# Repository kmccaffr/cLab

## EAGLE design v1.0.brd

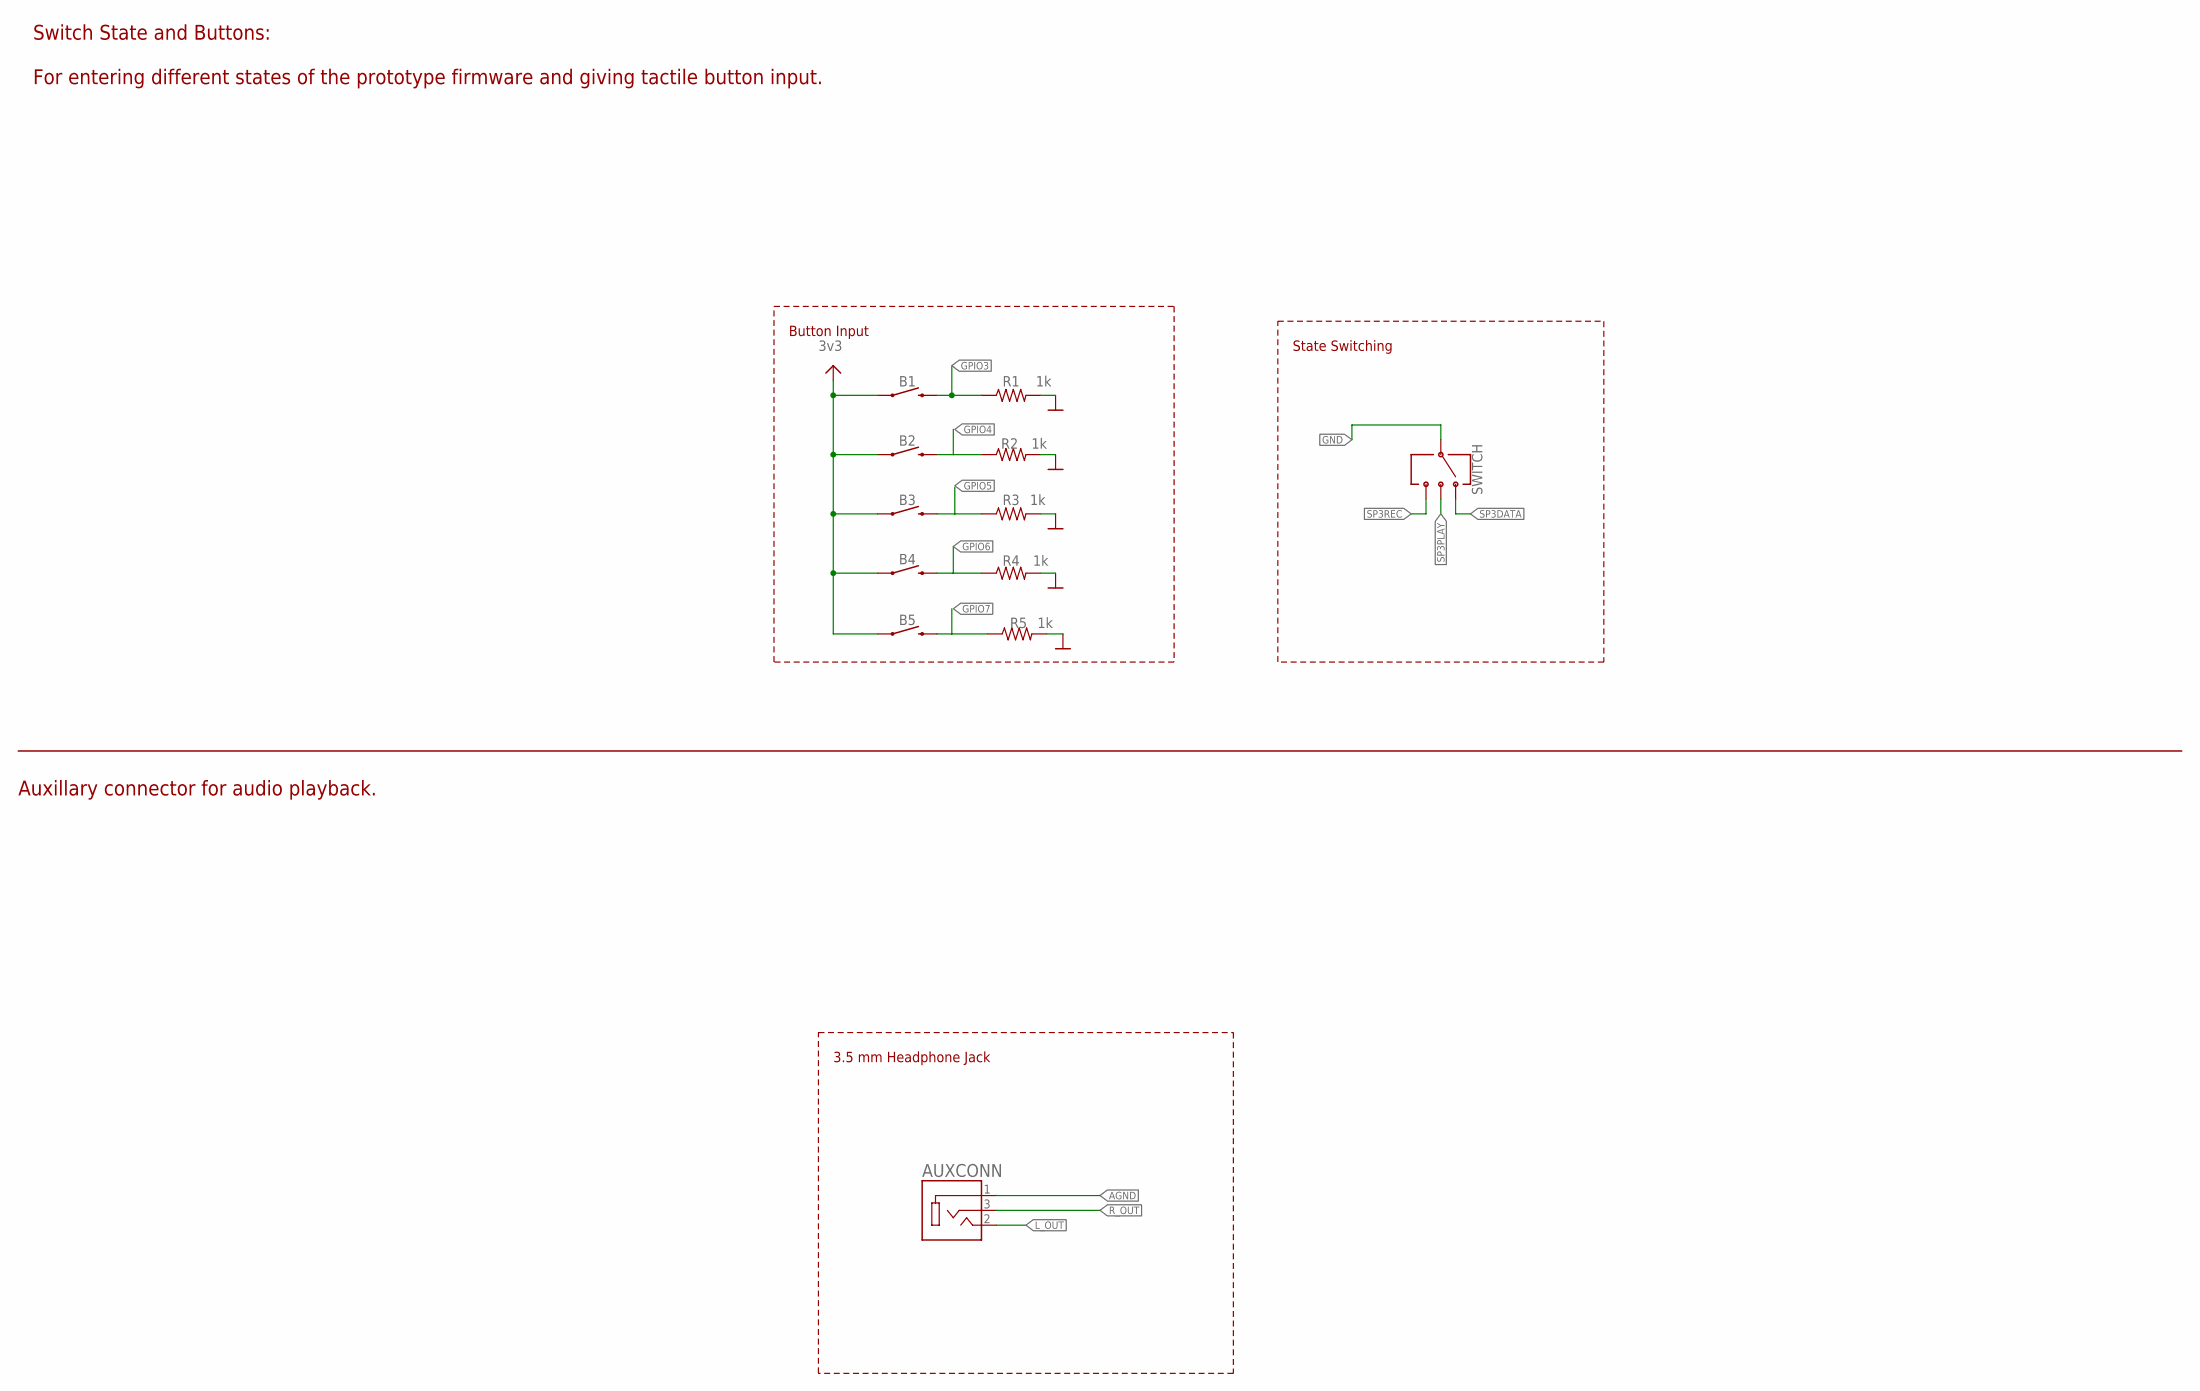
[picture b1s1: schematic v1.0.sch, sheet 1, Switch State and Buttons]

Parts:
AUXCONN: 3.5MM_AUX_JACK; !_SJ-3523-SMT-TR_CUI_SJ-3523-SMT-TR
B1, B2, B3, B4, B5: MOMENTARY-SWITCH-SPST-SMD-6.2MM-TALL; !_TACTILE_SWITCH_SMD_6.2MM_TALL
R1, R2, R3, R4, R5: 1k; !_0603
SWITCH: SWITCH-SP3T-SMD; !SWITCH_SP3T_SMD

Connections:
3.3V: B1.A2 (1), B2.A2 (1), B3.A2 (1), B4.A2 (1), B5.A2 (1); also elsewhere on the board
AGND: AUXCONN.1; also elsewhere on the board
GND: R1.2, R2.2, R3.2, R4.2, R5.2, SWITCH.3; also elsewhere on the board
GPIO3: B1.B2 (2), R1.1; also elsewhere on the board
GPIO4: B2.B2 (2), R2.1; also elsewhere on the board
GPIO5: B3.B2 (2), R3.1; also elsewhere on the board
GPIO6: B4.B2 (2), R4.1; also elsewhere on the board
GPIO7: B5.B2 (2), R5.1; also elsewhere on the board
L_OUT: AUXCONN.2; also elsewhere on the board
R_OUT: AUXCONN.3; also elsewhere on the board
SP3DATA: SWITCH.1; also elsewhere on the board
SP3PLAY: SWITCH.2; also elsewhere on the board
SP3REC: SWITCH.4; also elsewhere on the board

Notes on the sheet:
Button Input
State Switching
3v3
Switch State and Buttons: For entering different states of the prototype firmware and giving tactile button input.
3.5 mm Headphone Jack
Auxillary connector for audio playback.

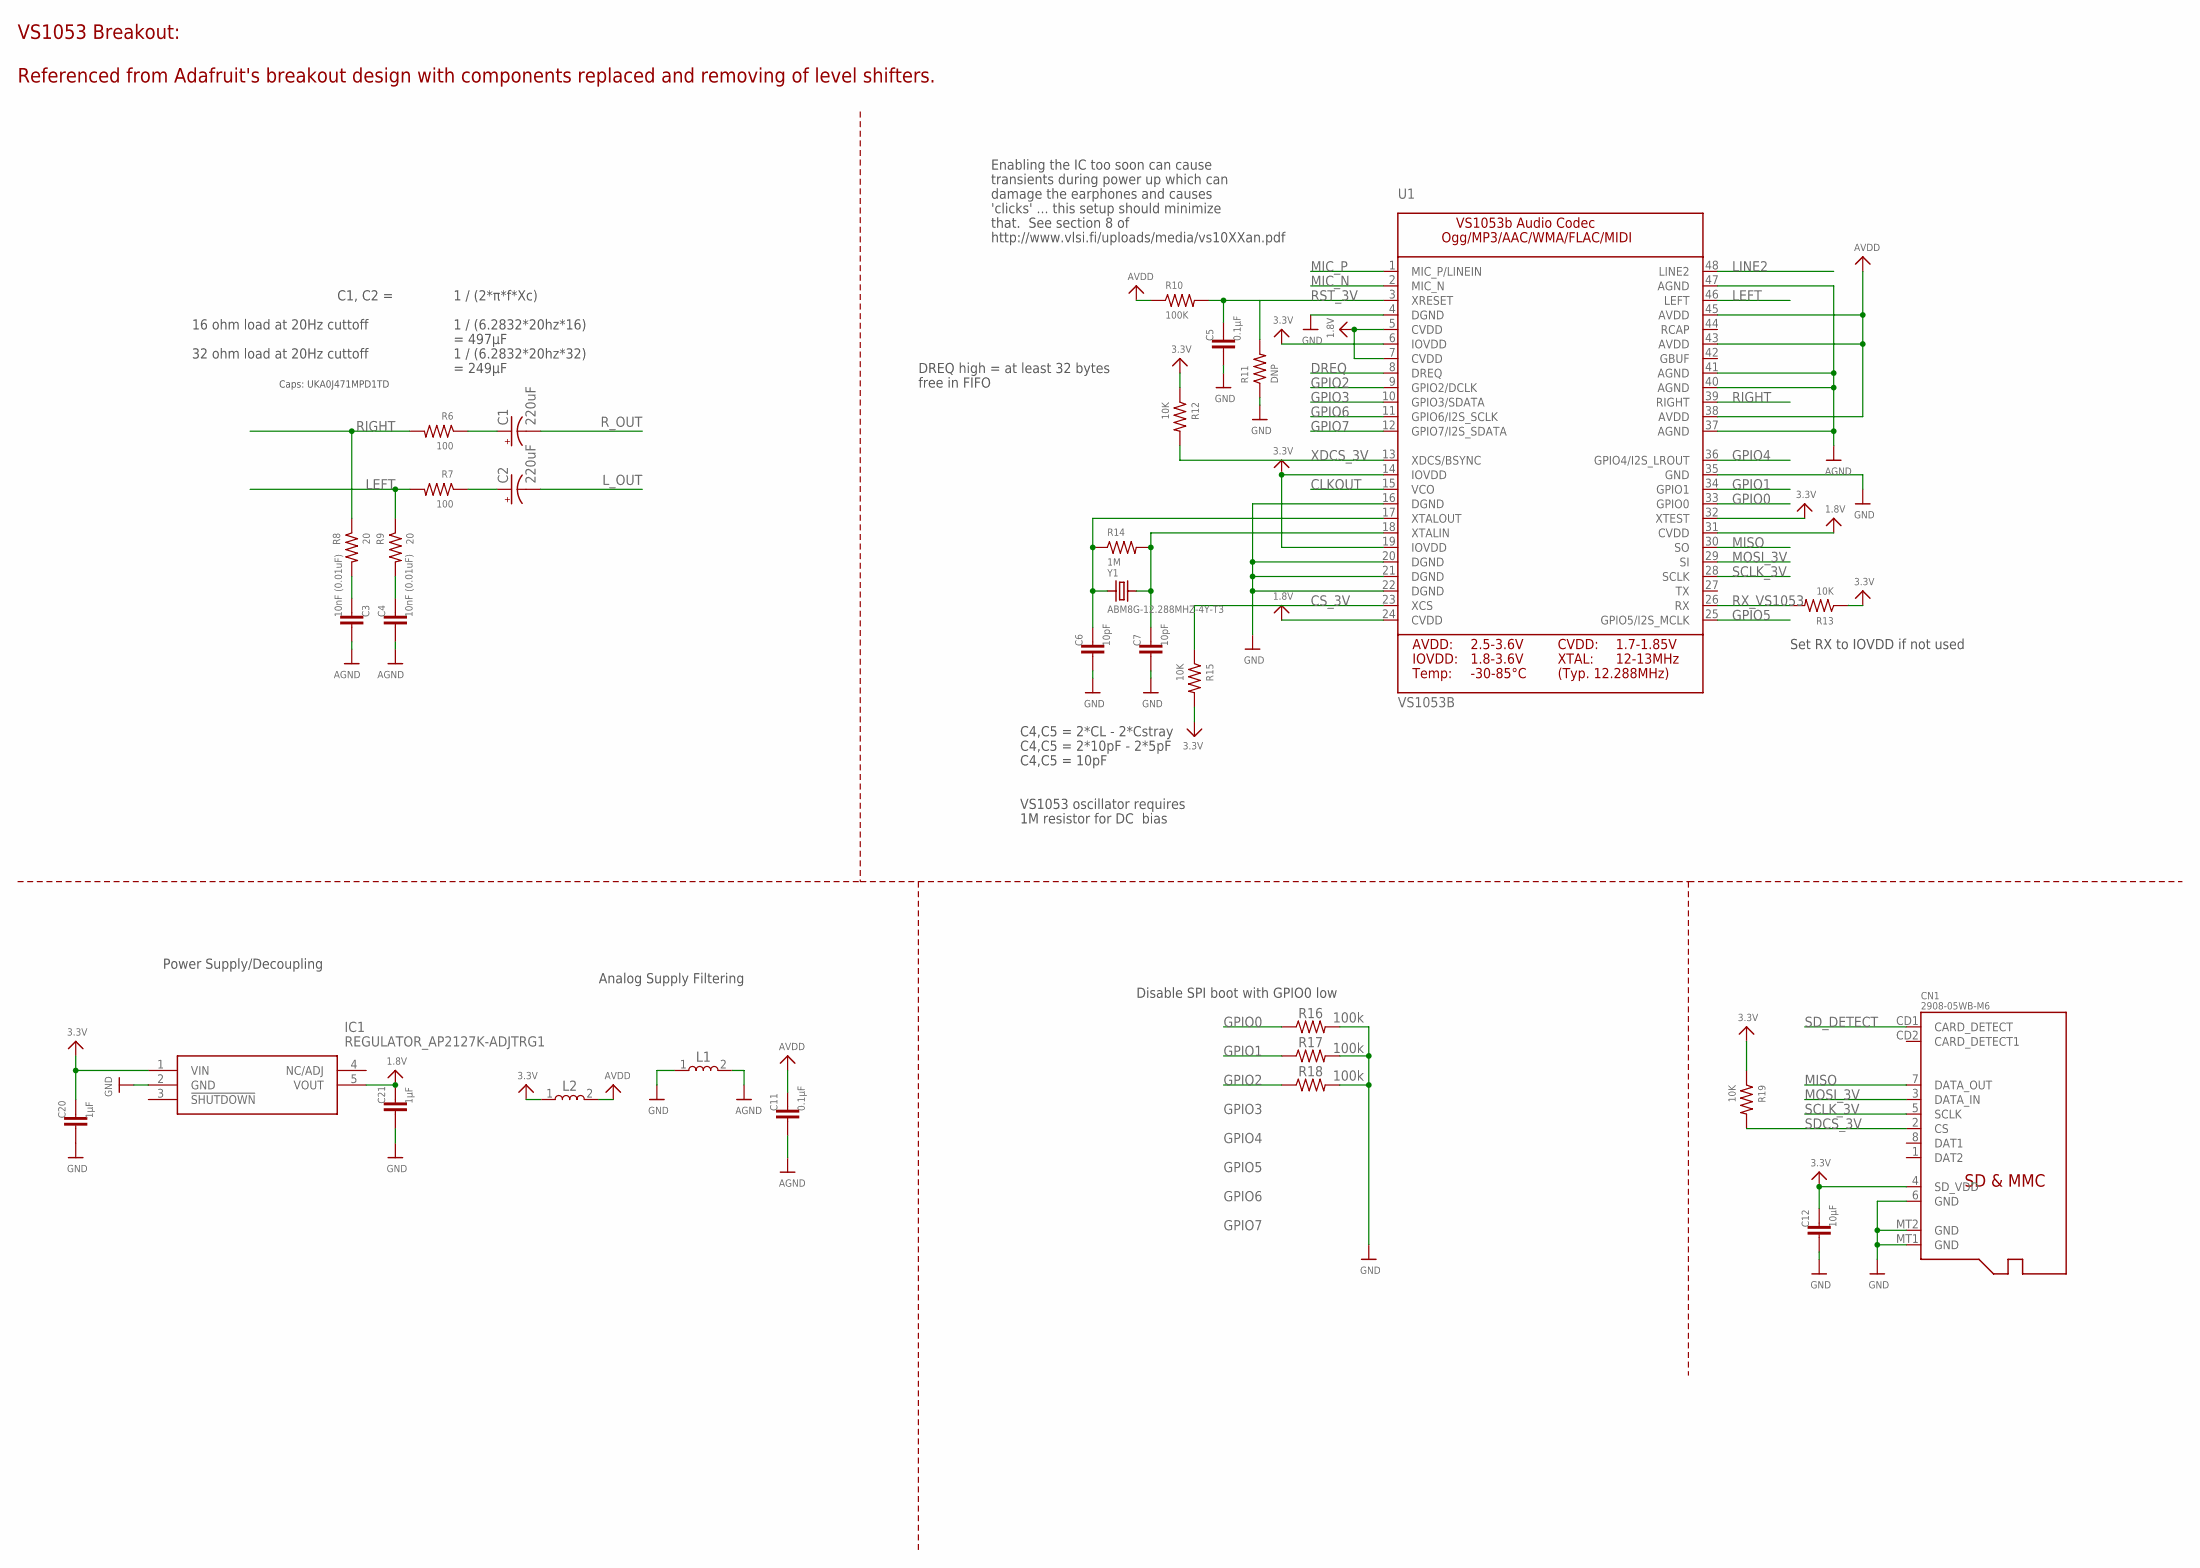
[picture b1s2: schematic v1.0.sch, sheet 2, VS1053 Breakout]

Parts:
C1, C2: 220uF; !_PANASONIC_E
C3, C4: 10nF (0.01uF); !_0603
C5, C11: 0.1µF; !_0603
C6, C7: 10pF; !_0603
C12: 10µF; !_0603
C20, C21: 1µF; !_0603
CN1: 2908-05WB-M6; !_MICROSD
IC1: REGULATOR_AP2127K-ADJTRG1; !_AP2127K-ADJTRG1_SOT95P282X145-5N
L1, L2: FERRITE_BEAD0805; !_FERRITE_0805
R6, R7: 100; !_0603
R8, R9: 20; !_0603
R10: 100K; !_0603
R11: DNP; !_0603
R12, R13, R15, R19: 10K; !_0603
R14: 1M; !_0603
R16, R17, R18: 100k; !_0603
U1: VS1053B; !VS1053_LQFP48
Y1: ABM8G-12.288MHZ-4Y-T3; !_CRYSTAL_3.2X2.5

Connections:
1.8V: C21.1, IC1.5 (VOUT), U1.5 (CVDD), U1.7 (CVDD), U1.24 (CVDD), U1.31 (CVDD)
3.3V: C12.1, C20.1, CN1.4 (SD_VDD), IC1.1 (VIN), L2.1, R12.1, R13.1, R15.2, R19.1, U1.6 (IOVDD), U1.14 (IOVDD), U1.19 (IOVDD), U1.32 (XTEST); also elsewhere on the board
AGND: C3.2, C4.2, C11.2, L1.2, U1.37 (AGND), U1.40 (AGND), U1.41 (AGND), U1.47 (AGND); also elsewhere on the board
AVDD: C11.1, L2.2, R10.1, U1.38 (AVDD), U1.43 (AVDD), U1.45 (AVDD)
CLKOUT: U1.15 (VCO)
CS_3V: R15.1, U1.23 (XCS); also elsewhere on the board
DREQ: U1.8 (DREQ); also elsewhere on the board
GND: C5.2, C6.2, C7.2, C12.2, C20.2, C21.2, CN1.6 (GND), CN1.MT1 (GND), CN1.MT2 (GND), IC1.2 (GND), L1.1, R11.1, R16.2, R17.2, R18.2, U1.4 (DGND), U1.16 (DGND), U1.20 (DGND), U1.21 (DGND), U1.22 (DGND), U1.35 (GND); also elsewhere on the board
GPIO0: R16.1, U1.33 (GPIO0)
GPIO1: R17.1, U1.34 (GPIO1)
GPIO2: R18.1, U1.9 (GPIO2/DCLK)
GPIO3: U1.10 (GPIO3/SDATA); also elsewhere on the board
GPIO4: U1.36 (GPIO4/I2S_LROUT); also elsewhere on the board
GPIO5: U1.25 (GPIO5/I2S_MCLK); also elsewhere on the board
GPIO6: U1.11 (GPIO6/I2S_SCLK); also elsewhere on the board
GPIO7: U1.12 (GPIO7/I2S_SDATA); also elsewhere on the board
LEFT: R7.2, R9.1, U1.46 (LEFT)
LEFT_FILTERED: C2.+, R7.1
LINE2: U1.48 (LINE2)
L_OUT: C2.-; also elsewhere on the board
MIC_N: U1.2 (MIC_N)
MIC_P: U1.1 (MIC_P/LINEIN); also elsewhere on the board
MISO: CN1.7 (DATA_OUT), U1.30 (SO); also elsewhere on the board
MOSI_3V: CN1.3 (DATA_IN), U1.29 (SI); also elsewhere on the board
unnamed: C6.1, R14.1, U1.17 (XTALOUT), Y1.1
unnamed: C7.1, R14.2, U1.18 (XTALIN), Y1.2
unnamed: C4.1, R9.2
unnamed: C3.1, R8.2
RIGHT: R6.2, R8.1, U1.39 (RIGHT)
RIGHT_FILTERED: C1.+, R6.1
RST_3V: C5.1, R10.2, R11.2, U1.3 (XRESET); also elsewhere on the board
RX_VS1053: R13.2, U1.26 (RX)
R_OUT: C1.-; also elsewhere on the board
SCLK_3V: CN1.5 (SCLK), U1.28 (SCLK); also elsewhere on the board
SDCS_3V: CN1.2 (CS), R19.2; also elsewhere on the board
SD_DETECT: CN1.CD1 (CARD_DETECT)
XDCS_3V: R12.2, U1.13 (XDCS/BSYNC); also elsewhere on the board

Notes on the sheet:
Analog Supply Filtering
C4,C5 = 2*CL - 2*Cstray
C4,C5 = 2*10pF - 2*5pF
C4,C5 = 10pF
VS1053 oscillator requires
1M resistor for DC bias
Set RX to IOVDD if not used
DREQ high = at least 32 bytes
Power Supply/Decoupling
transients during power up which can
damage the earphones and causes
'clicks' ... this setup should minimize
that. See section 8 of
http://www.vlsi.fi/uploads/media/vs10XXan.pdf
Enabling the IC too soon can cause
free in FIFO
Disable SPI boot with GPIO0 low
1 / (2*π*f*Xc)
16 ohm load at 20Hz cuttoff
1 / (6.2832*20hz*16)
C1, C2 =
= 497µF
32 ohm load at 20Hz cuttoff
1 / (6.2832*20hz*32)
= 249µF
Caps: UKA0J471MPD1TD
VS1053 Breakout: Referenced from Adafruit's breakout design with components replaced and removing of level shifters.

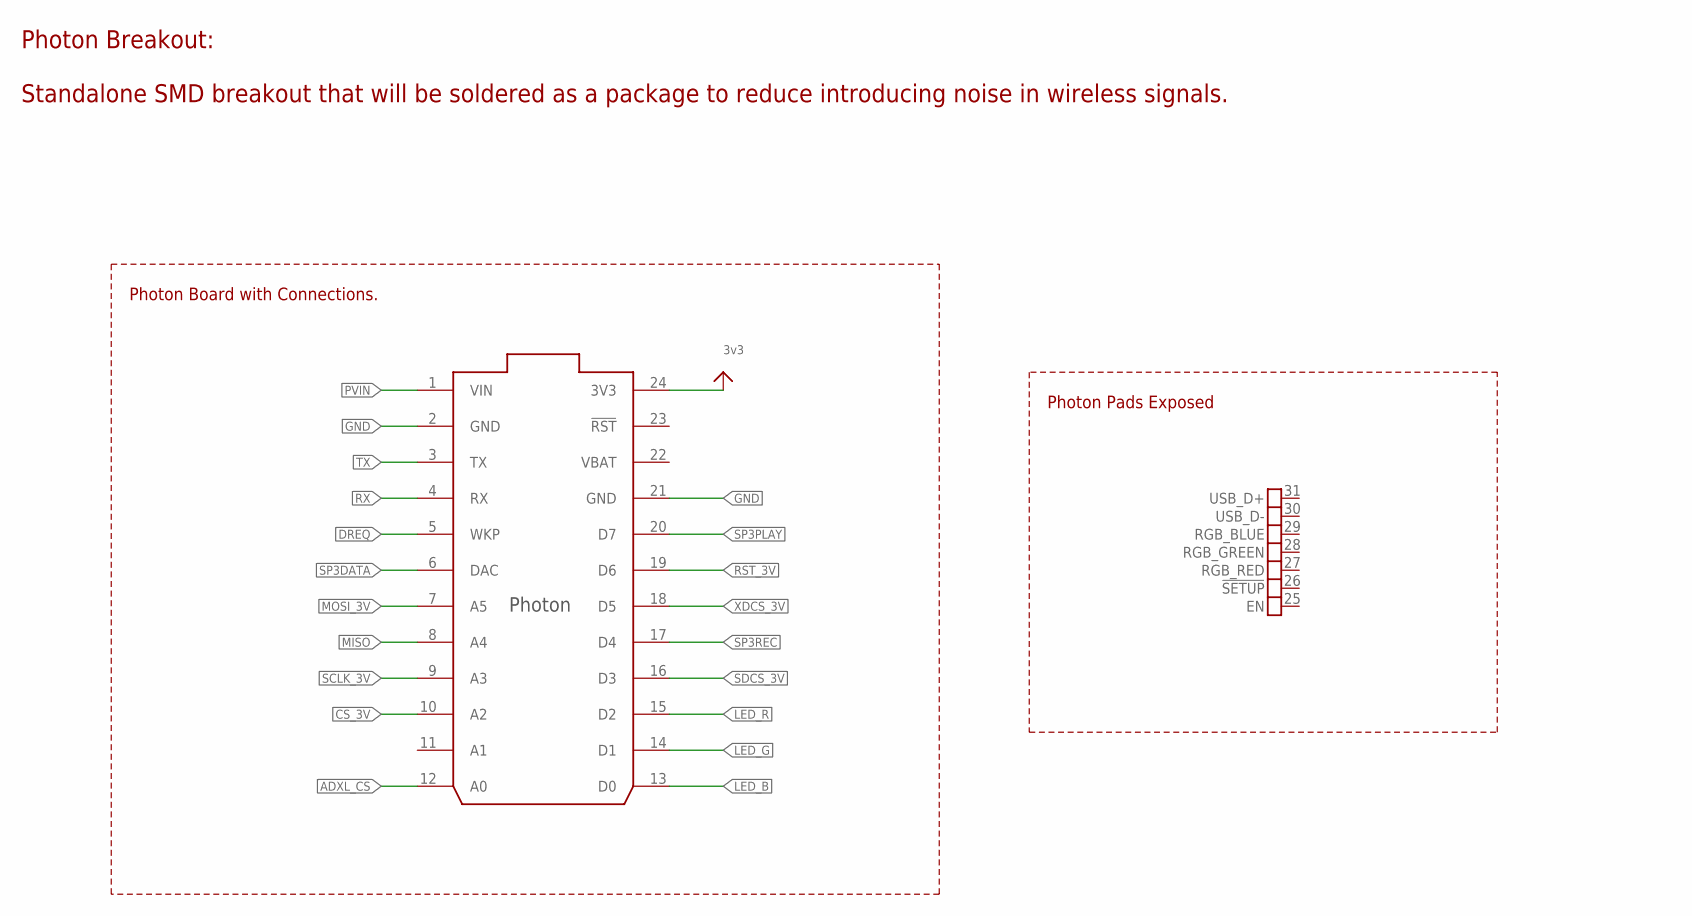
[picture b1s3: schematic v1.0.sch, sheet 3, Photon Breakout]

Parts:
U$1: PARTICLE-DEVICES_PHOTON_SMD; !_PARTICLE-DEVICES_PHOTON_SMD

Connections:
3.3V: U$1.24 (3V3); also elsewhere on the board
ADXL_CS: U$1.12 (A0); also elsewhere on the board
CS_3V: U$1.10 (A2); also elsewhere on the board
DREQ: U$1.5 (WKP); also elsewhere on the board
GND: U$1.2 (GND), U$1.21 (GND); also elsewhere on the board
LED_B: U$1.13 (D0); also elsewhere on the board
LED_G: U$1.14 (D1); also elsewhere on the board
LED_R: U$1.15 (D2); also elsewhere on the board
MISO: U$1.8 (A4); also elsewhere on the board
MOSI_3V: U$1.7 (A5); also elsewhere on the board
PVIN: U$1.1 (VIN); also elsewhere on the board
RST_3V: U$1.19 (D6); also elsewhere on the board
RX: U$1.4 (RX); also elsewhere on the board
SCLK_3V: U$1.9 (A3); also elsewhere on the board
SDCS_3V: U$1.16 (D3); also elsewhere on the board
SP3DATA: U$1.6 (DAC); also elsewhere on the board
SP3PLAY: U$1.20 (D7); also elsewhere on the board
SP3REC: U$1.17 (D4); also elsewhere on the board
TX: U$1.3 (TX); also elsewhere on the board
VBAT: U$1.22 (VBAT)
XDCS_3V: U$1.18 (D5); also elsewhere on the board

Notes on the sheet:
3v3
Photon Breakout: Standalone SMD breakout that will be soldered as a package to reduce introducing noise in wireless signals.
Photon Board with Connections.
Photon Pads Exposed

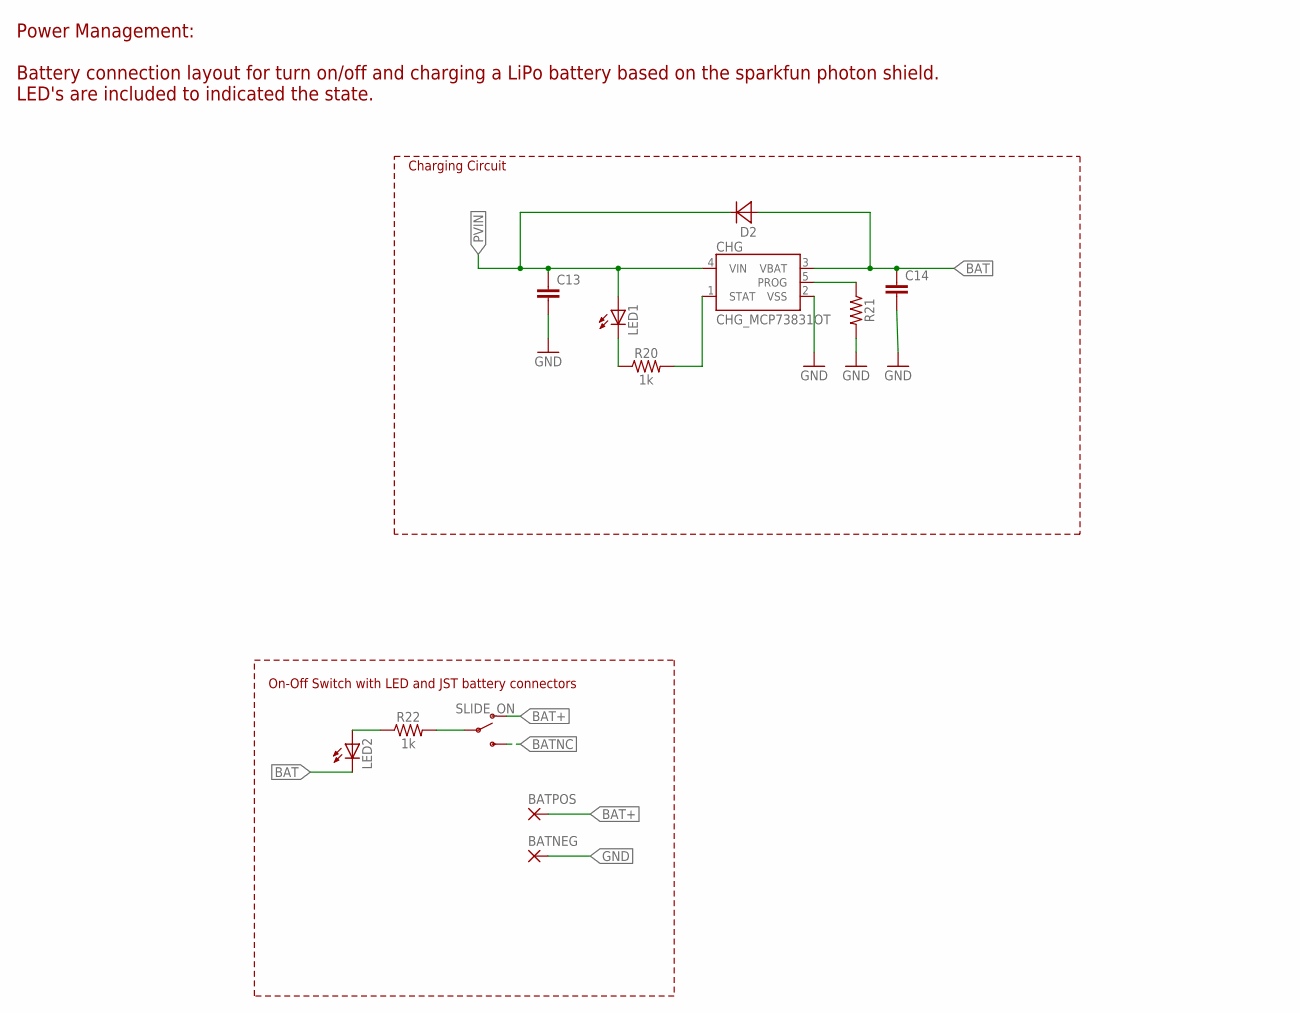
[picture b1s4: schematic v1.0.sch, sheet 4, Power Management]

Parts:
BATNEG: SMD5; SMD2,54-5,08
BATPOS: SMD5; SMD2,54-5,08
C13, C14: 4.7uF; !_0603
CHG: CHG_MCP73831OT; !_SOT23-5
D2: DIODE_MBRA140T3; !_DIODE_SMA
LED1, LED2: PASSIVE_LED; !_LED_0603
R20, R22: 1k; !_0603
R21: 10k; !_0603
SLIDE_ON: PASSIVE_SLIDE_SWITCHES; !_SWITCH_PCM12SMTR

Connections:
BAT: C14.1, CHG.3 (VBAT), D2.A, LED2.C
BAT+: BATPOS.1, SLIDE_ON.O
BATNC: SLIDE_ON.S
GND: BATNEG.1, C13.2, C14.2, CHG.2 (VSS), R21.2; also elsewhere on the board
unnamed: CHG.1 (STAT), R20.2
unnamed: LED1.C, R20.1
unnamed: R22.2, SLIDE_ON.P
unnamed: LED2.A, R22.1
unnamed: CHG.5 (PROG), R21.1
PVIN: C13.1, CHG.4 (VIN), D2.C, LED1.A; also elsewhere on the board

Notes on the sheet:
On-Off Switch with LED and JST battery connectors
Charging Circuit
Power Management: Battery connection layout for turn on/off and charging a LiPo battery based on the sparkfun photon shield. LED's are included to indicated the state.

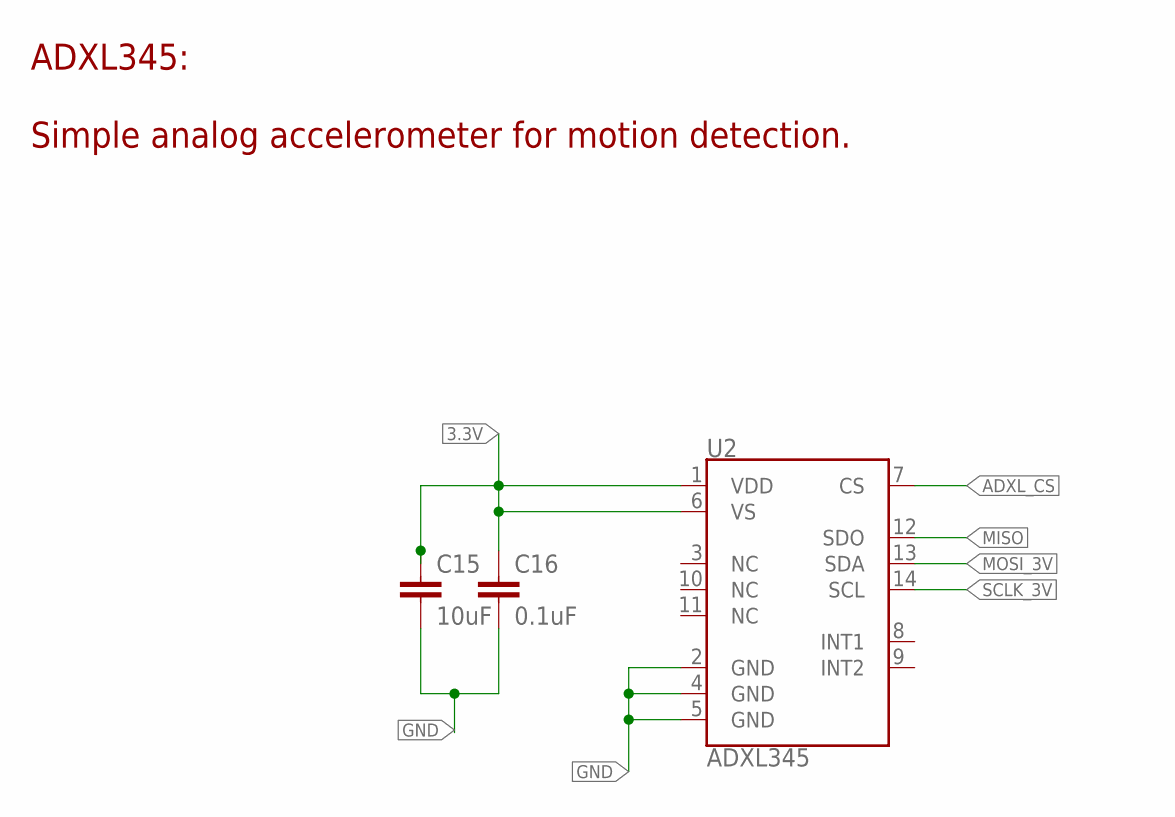
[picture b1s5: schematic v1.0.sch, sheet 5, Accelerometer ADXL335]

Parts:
C15: 10uF; !_0603
C16: 0.1uF; !_0603
U2: ADXL345; !_ADXL345_LGA-14

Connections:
3.3V: C15.1, C16.1, U2.1 (VDD), U2.6 (VS); also elsewhere on the board
ADXL_CS: U2.7 (CS); also elsewhere on the board
GND: C15.2, C16.2, U2.2 (GND), U2.4 (GND), U2.5 (GND); also elsewhere on the board
MISO: U2.12 (SDO); also elsewhere on the board
MOSI_3V: U2.13 (SDA); also elsewhere on the board
SCLK_3V: U2.14 (SCL); also elsewhere on the board

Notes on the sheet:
ADXL345: Simple analog accelerometer for motion detection.

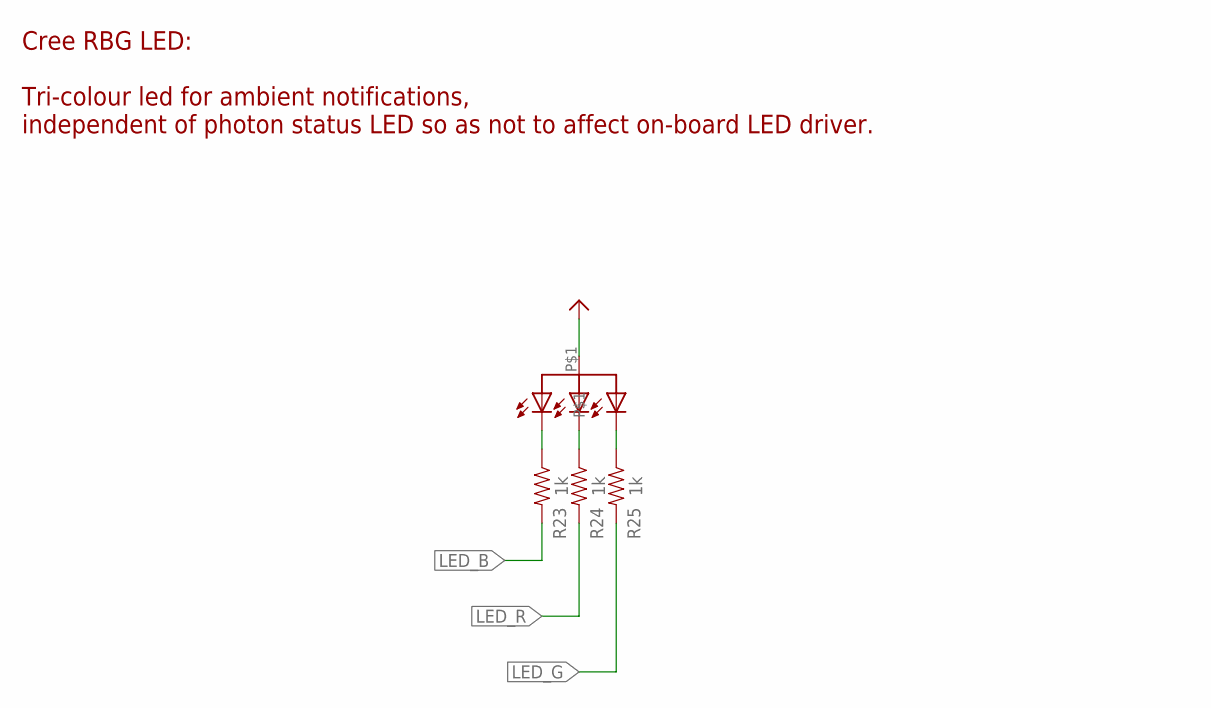
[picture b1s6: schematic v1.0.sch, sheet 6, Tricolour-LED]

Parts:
LED3: LED_TRICOLOR_3.2X2.8; !_LED_3.2X2.8
R23, R24, R25: 1k; !_0603

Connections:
3.3V: LED3.P$1; also elsewhere on the board
LED_B: R23.2; also elsewhere on the board
LED_G: R25.2; also elsewhere on the board
LED_R: R24.2; also elsewhere on the board
unnamed: LED3.P$2, R23.1
unnamed: LED3.P$3, R24.1
unnamed: LED3.P$4, R25.1

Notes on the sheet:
Cree RBG LED: Tri-colour led for ambient notifications, independent of photon status LED so as not to affect on-board LED driver.

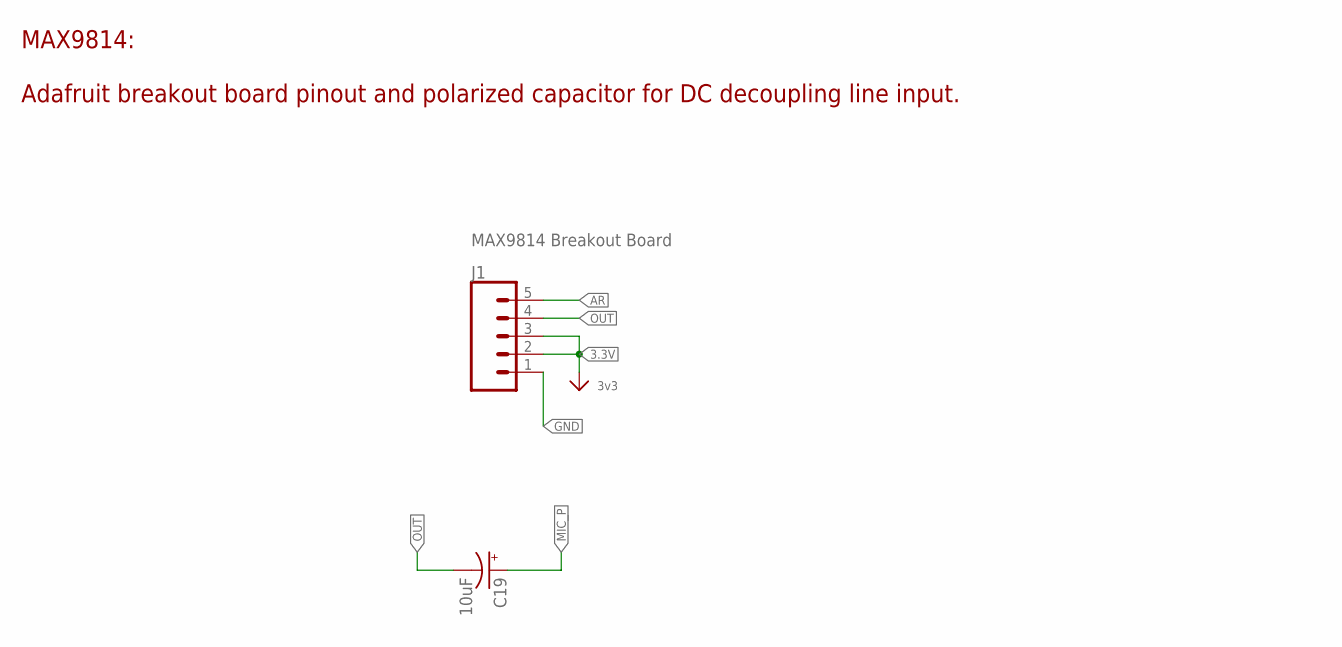
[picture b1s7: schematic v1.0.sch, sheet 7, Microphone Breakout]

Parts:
C19: 10uF; !_PARTICLE_PC0603
J1: CONNECTORS_CONN_05; !_CONNECTORS_1X05

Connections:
3.3V: J1.2, J1.3; also elsewhere on the board
AR: J1.5
GND: J1.1; also elsewhere on the board
MIC_P: C19.A (+); also elsewhere on the board
OUT: C19.C (-), J1.4

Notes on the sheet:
MAX9814 Breakout Board
3v3
MAX9814: Adafruit breakout board pinout and polarized capacitor for DC decoupling line input.

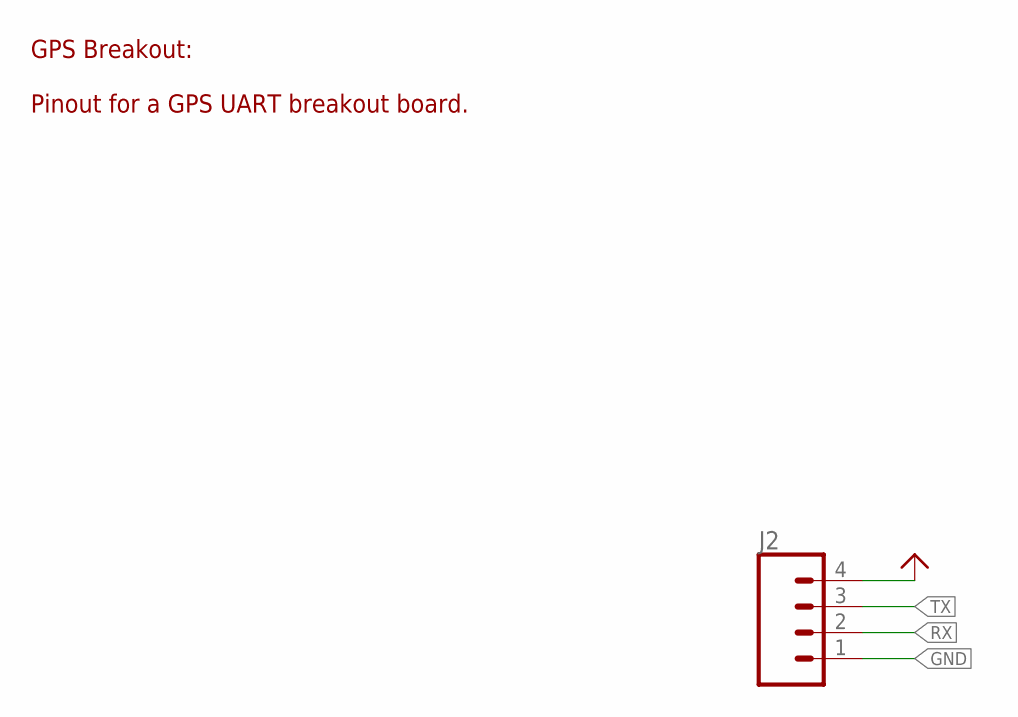
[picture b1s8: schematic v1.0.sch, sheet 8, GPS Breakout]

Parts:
J2: CONNECTORS_CONN_04; !_CONNECTORS_1X04

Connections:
3.3V: J2.4; also elsewhere on the board
GND: J2.1; also elsewhere on the board
RX: J2.2; also elsewhere on the board
TX: J2.3; also elsewhere on the board

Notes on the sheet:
GPS Breakout: Pinout for a GPS UART breakout board.

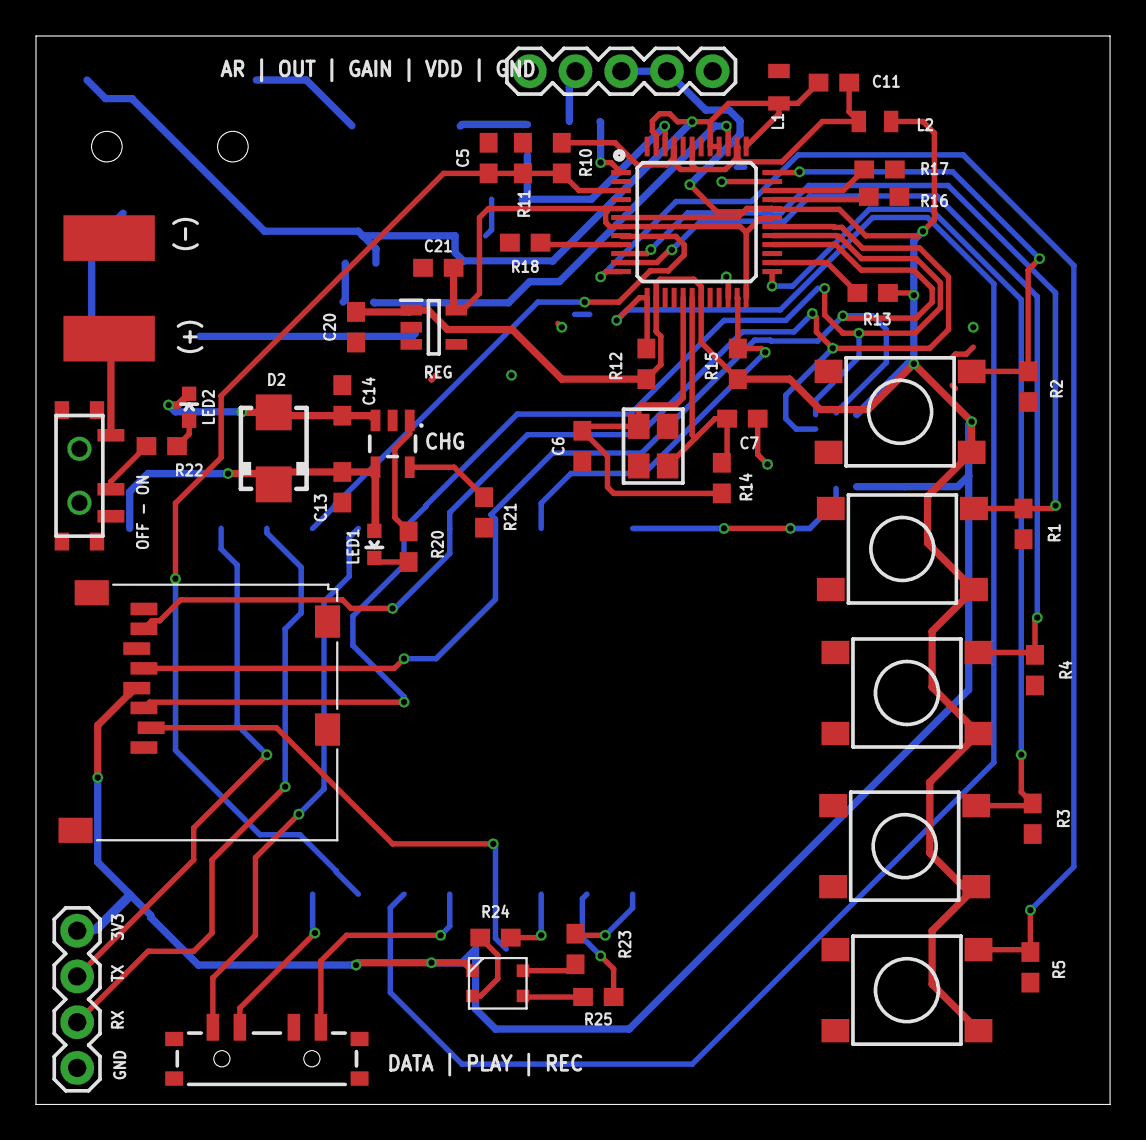
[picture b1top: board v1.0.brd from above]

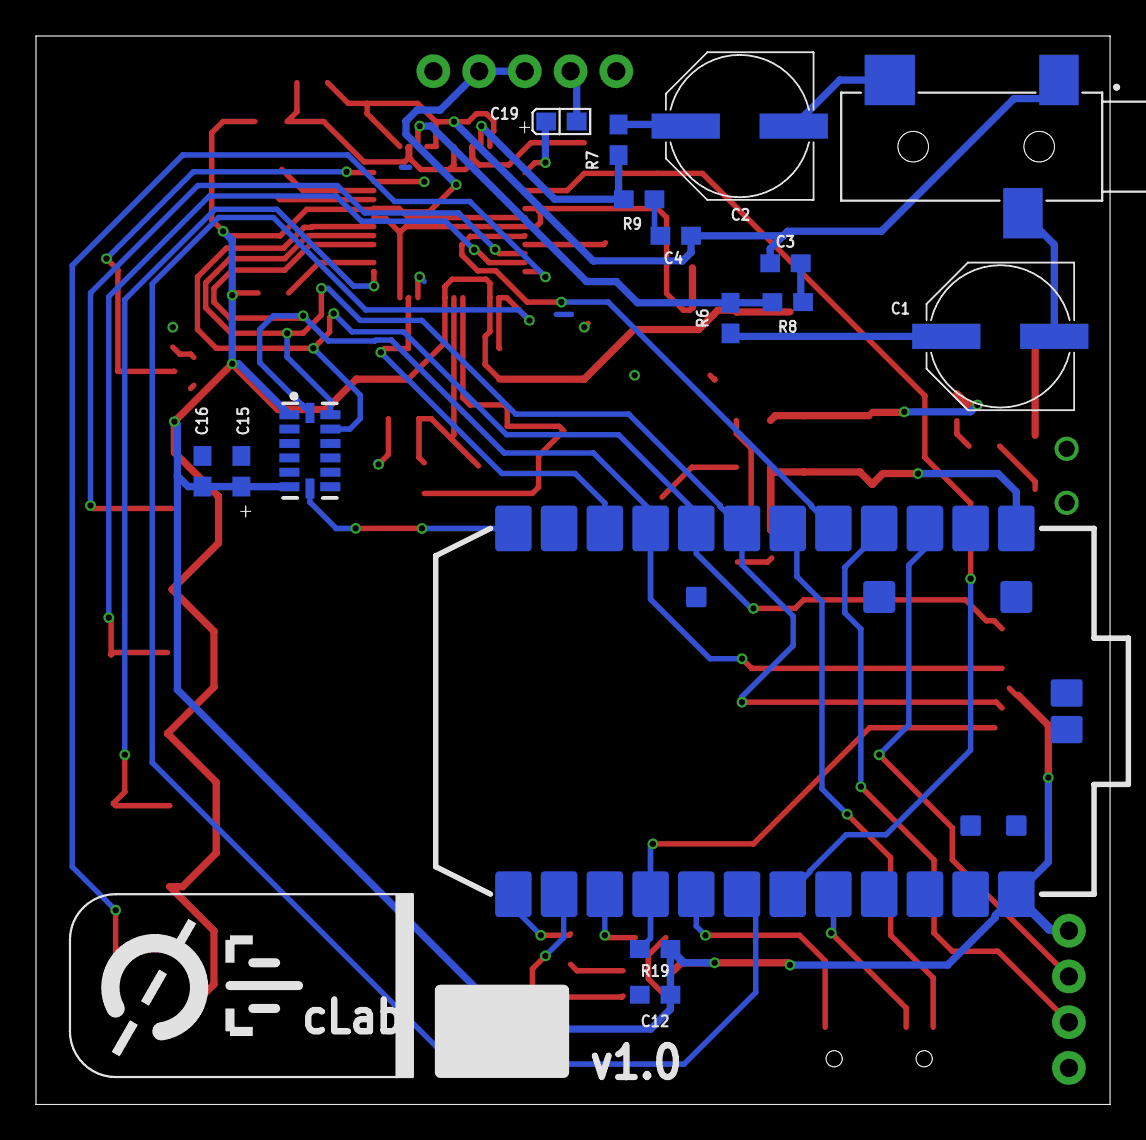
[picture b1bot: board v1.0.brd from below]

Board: 2 copper layers, 59.7 x 59.4 mm, 66 parts (16 on the bottom side), 54 nets.

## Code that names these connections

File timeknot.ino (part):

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#define VS1053_CS       A2      // VS1053 chip select pin (output)
#define VS1053_DCS      D5      // VS1053 Data/command select pin (output)
#define CARDCS          D3      // Card chip select pin
#define DREQ            WKP     // VS1053 Data request, ideally an Interrupt pin

// Switch state pins
#define SP3REC          D4      // For recording audio messsages and writing to FTP server
#define SP3PLAY         D7      // For playback of audio
#define SP3DATA         DAC     // For buffering of FTP server and receiving data

// Button input variables
#define BUTTON_1        3        // Record(REC) / Play and Pause (PLAY) / Manually check data (DATA)
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#define BUTTON_5        7        // Volume Down (PLAY)

// RGB LED pins
#define LED_R           D2      // Red LED in sensor
#define LED_G           D1      // Green LED in sensor
#define LED_B           D0      // Blue LED in sensor

// ADXL pins
#define ADXL_CS         A0      // SPI chip-select pin for accelerometer

// Define bitshifting(or casting) for recording
#define _BV(bit) (1 << (bit))
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

// LED
pinMode(LED_R, OUTPUT);
pinMode(LED_G, OUTPUT);
pinMode(LED_B, OUTPUT);
digitalWrite(LED_R, HIGH);
digitalWrite(LED_B, HIGH);
digitalWrite(LED_G, HIGH);
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prevButtonState = LOW;

// Setting state switch pin mode
pinMode(SP3REC, INPUT_PULLUP);
pinMode(SP3DATA, INPUT_PULLUP);
pinMode(SP3PLAY, INPUT_PULLUP);

// Setting VS1053 GPIO pin mode
musicPlayer.GPIO_pinMode(BUTTON_1, INPUT);
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/************************************************************* MOTION ARTIFACT CHECK */
if (artifactMotion)
{
pinMode(ADXL_CS, OUTPUT);
}
/************************************************************* MOTION ARTIFACT CHECK */
delay(5000);
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
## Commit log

2019-09-15 Add files via upload
    Adding files from bitbucket private repository for sample portfolio.
    Files: Timeknot artifact code (not included are libraries and Spark/Kinetic artifact code with small variations)
    Eagle board file revision 1.1
